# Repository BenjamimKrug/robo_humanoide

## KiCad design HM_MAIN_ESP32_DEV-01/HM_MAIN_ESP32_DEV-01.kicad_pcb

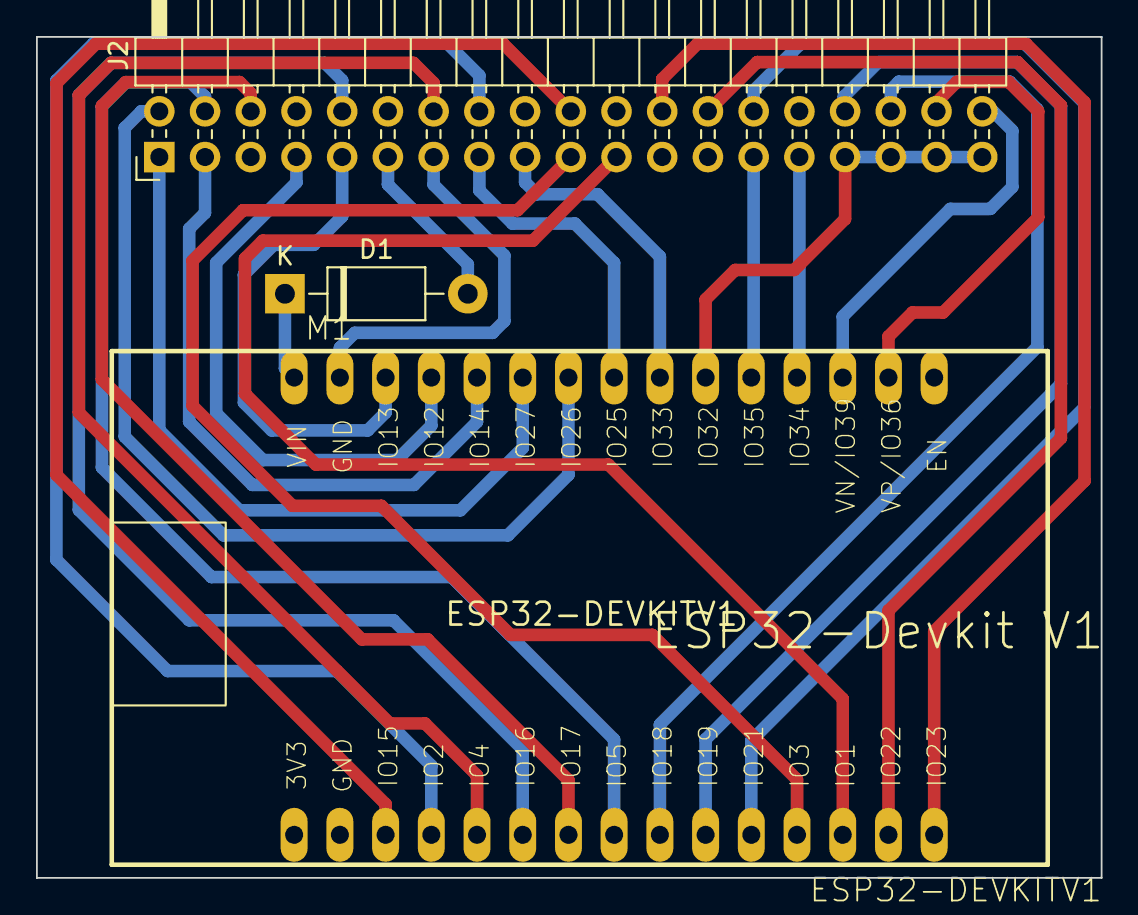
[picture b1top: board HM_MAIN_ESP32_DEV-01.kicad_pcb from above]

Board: 2 copper layers, 59.1 x 46.7 mm, 3 parts (0 on the bottom side), 28 nets.

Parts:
D1: 1N4007; D_DO-41_SOD81_P10.16mm_Horizontal
J2: Conn_02x19_Odd_Even; PinHeader_2x19_P2.54mm_Horizontal
M1: ESP32-DEVKITV1

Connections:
GND: J2.13, M1.GND@1 (GND)
I_SENS: J2.27, M1.D35 (IO35)
L_ANK_PWM: J2.1, M1.D27 (IO27)
L_ELB_PWM: J2.10, M1.D16 (IO16)
L_FT_ANGLE: J2.38, M1.D39 (VN-IO39)
L_FT_PWM: J2.2, M1.D26 (IO26)
L_HP_PWM: J2.9, M1.D13 (IO13)
L_KN_PWM: J2.3, M1.D14 (IO14)
L_SH_PWM: J2.6, M1.D17 (IO17)
L_TG_PWM: J2.7, M1.D12 (IO12)
L_TX_PWM: J2.4, M1.D5 (IO5)
MAIN_RX: J2.19, M1.D3 (IO3)
MAIN_TX: J2.21, M1.D1 (IO1)
unnamed: D1.1 (K), M1.VIN
R_ANK_PWM: J2.26, M1.D22 (IO22)
R_ELB_PWM: J2.20, M1.D15 (IO15)
R_FT_ANGLE: J2.36, M1.D36 (VP-OI36)
R_FT_PWM: J2.24, M1.D23 (IO23)
R_HP_PWM: J2.34, M1.D18 (IO18)
R_KN_PWM: J2.28, M1.D21 (IO21)
R_SH_PWM: J2.16, M1.D2 (IO2)
R_TG_PWM: J2.32, M1.D19 (IO19)
R_TX_PWM: J2.14, M1.D4 (IO4)
SCL: J2.15, M1.D25 (IO25)
SDA: J2.17, M1.D33 (IO33)
SERVO_CONTROL: J2.31, J2.33, J2.35, J2.37, M1.D32 (IO32)
SERVO_VCC: D1.2 (A), J2.11
SHUTOFF: J2.29, M1.D34 (IO34)

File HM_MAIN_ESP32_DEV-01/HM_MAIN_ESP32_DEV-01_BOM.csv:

"Id";"Designador";"Footprint";"Quantidade";"Designação";"Fornecedor e referência";
1;"M1";"ESP32-DEVKITV1";1;"ESP32-DEVKITV1";;;
2;"D1";"D_DO-41_SOD81_P10.16mm_Horizontal";1;"1N4007";;;
3;"J2";"PinHeader_2x19_P2.54mm_Horizontal";1;"Conn_02x19_Odd_Even";;;

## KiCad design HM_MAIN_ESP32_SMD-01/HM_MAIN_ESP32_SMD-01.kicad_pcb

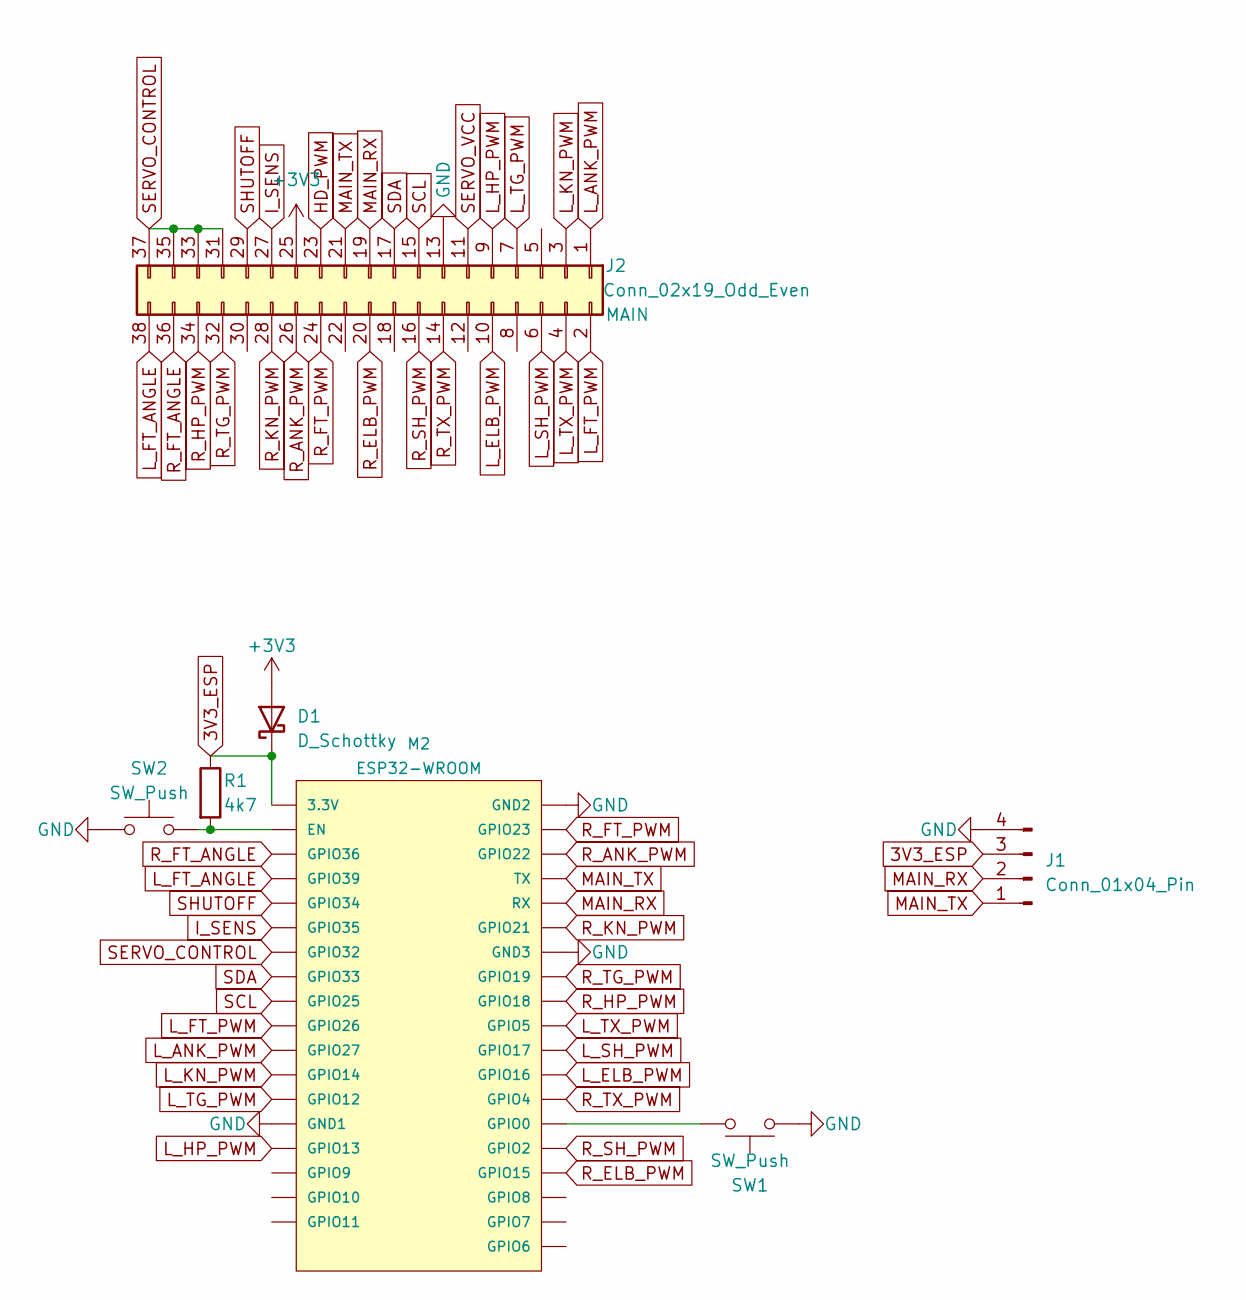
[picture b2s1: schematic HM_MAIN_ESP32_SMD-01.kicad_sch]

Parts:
D1: D_Schottky; D_A-405_P10.16mm_Horizontal
J1: Conn_01x04_Pin; PinHeader_1x04_P2.54mm_Horizontal
J2: Conn_02x19_Odd_Even; PinHeader_2x19_P2.54mm_Horizontal
M2: ESP32-WROOM
R1: 4k7; R_Axial_DIN0207_L6.3mm_D2.5mm_P7.62mm_Horizontal
SW1, SW2: SW_Push; SW_Tactile_SPST_Angled_PTS645Vx39-2LFS

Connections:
3V3_ESP: D1.1 (K), J1.3, M2.3V3 (3.3V), R1.1
+3V3: D1.2 (A), J2.25
GND: J1.4, J2.13, M2.GND1, M2.GND2, M2.GND3, SW1.1, SW2.1
HD_PWM: J2.23
I_SENS: J2.27, M2.IO35 (GPIO35)
L_ANK_PWM: J2.1, M2.IO27 (GPIO27)
L_ELB_PWM: J2.10, M2.IO16 (GPIO16)
L_FT_ANGLE: J2.38, M2.SENSOR_VN (GPIO39)
L_FT_PWM: J2.2, M2.IO26 (GPIO26)
L_HP_PWM: J2.9, M2.IO13 (GPIO13)
L_KN_PWM: J2.3, M2.IO14 (GPIO14)
L_SH_PWM: J2.6, M2.IO17 (GPIO17)
L_TG_PWM: J2.7, M2.IO12 (GPIO12)
L_TX_PWM: J2.4, M2.IO5 (GPIO5)
MAIN_RX: J1.2, J2.19, M2.RX
MAIN_TX: J1.1, J2.21, M2.TX
unnamed: M2.IO0 (GPIO0), SW1.2
unnamed: M2.EN, R1.2, SW2.2
R_ANK_PWM: J2.26, M2.IO22 (GPIO22)
R_ELB_PWM: J2.20, M2.IO15 (GPIO15)
R_FT_ANGLE: J2.36, M2.SENSOR_VP (GPIO36)
R_FT_PWM: J2.24, M2.IO23 (GPIO23)
R_HP_PWM: J2.34, M2.IO18 (GPIO18)
R_KN_PWM: J2.28, M2.IO21 (GPIO21)
R_SH_PWM: J2.16, M2.IO2 (GPIO2)
R_TG_PWM: J2.32, M2.IO19 (GPIO19)
R_TX_PWM: J2.14, M2.IO4 (GPIO4)
SCL: J2.15, M2.IO25 (GPIO25)
SDA: J2.17, M2.IO33 (GPIO33)
SERVO_CONTROL: J2.31, J2.33, J2.35, J2.37, M2.IO32 (GPIO32)
SERVO_VCC: J2.11
SHUTOFF: J2.29, M2.IO34 (GPIO34)

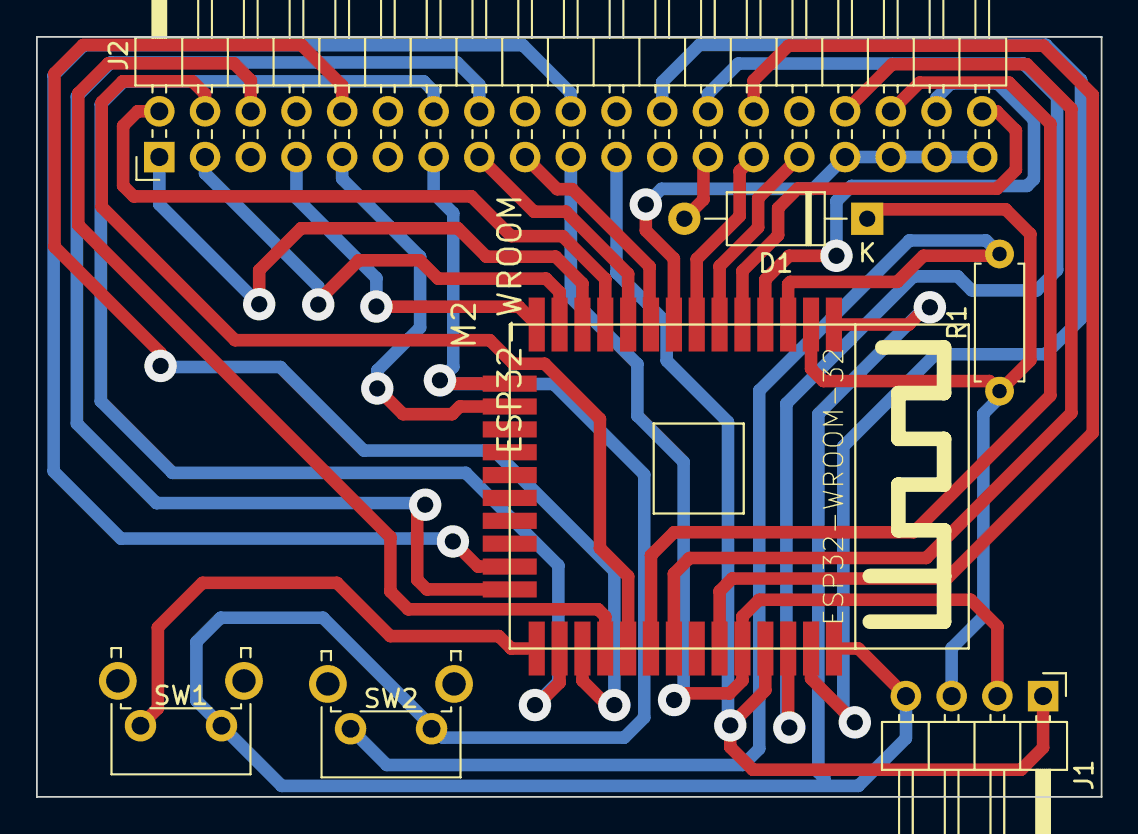
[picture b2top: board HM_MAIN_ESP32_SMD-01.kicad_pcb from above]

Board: 2 copper layers, 59.1 x 42.2 mm, 7 parts (0 on the bottom side), 30 nets.

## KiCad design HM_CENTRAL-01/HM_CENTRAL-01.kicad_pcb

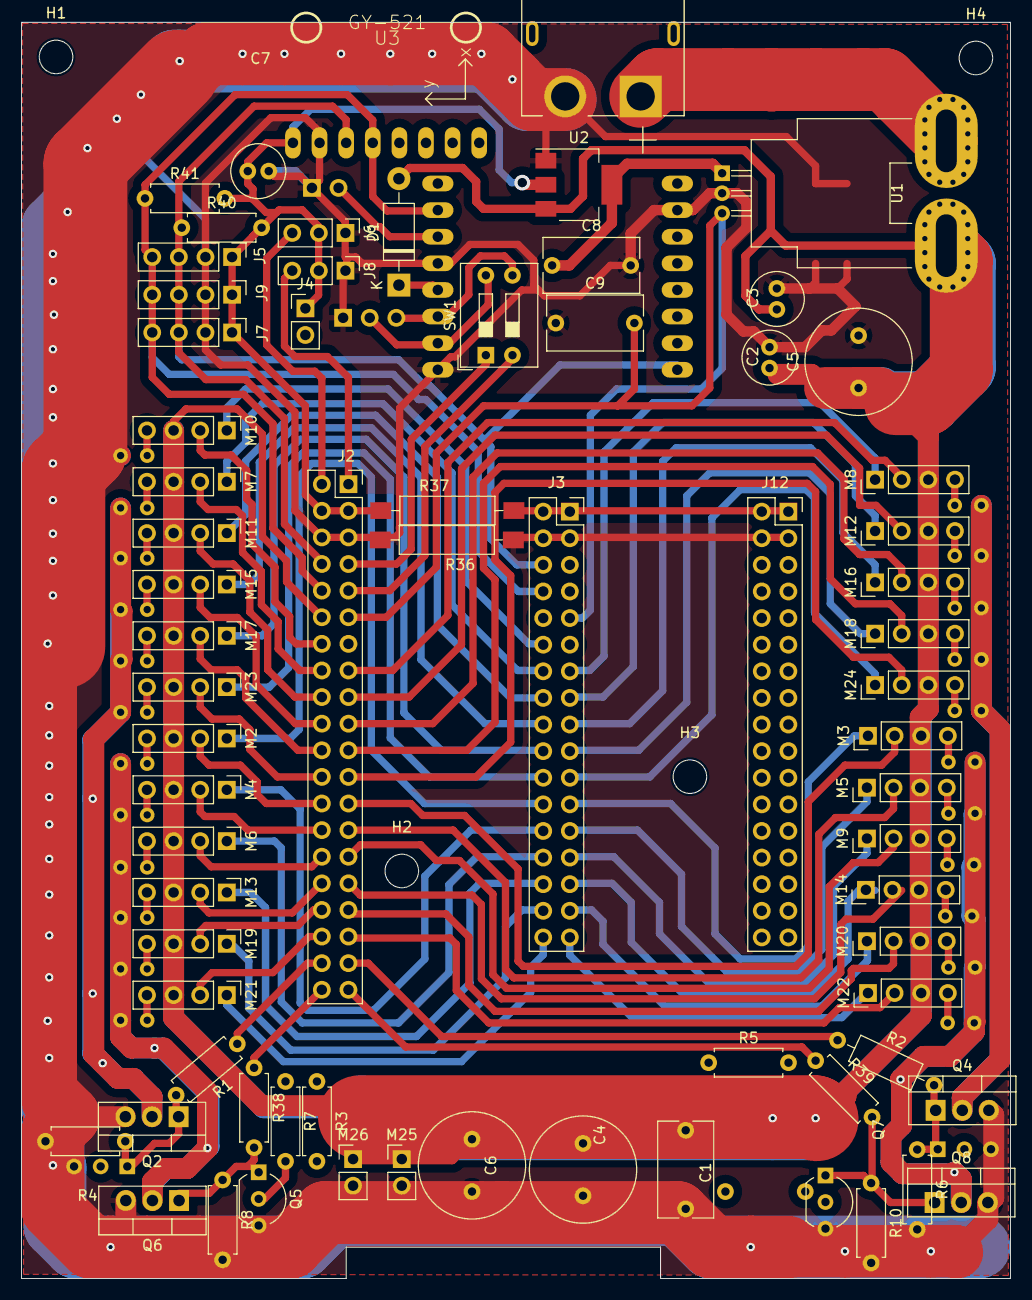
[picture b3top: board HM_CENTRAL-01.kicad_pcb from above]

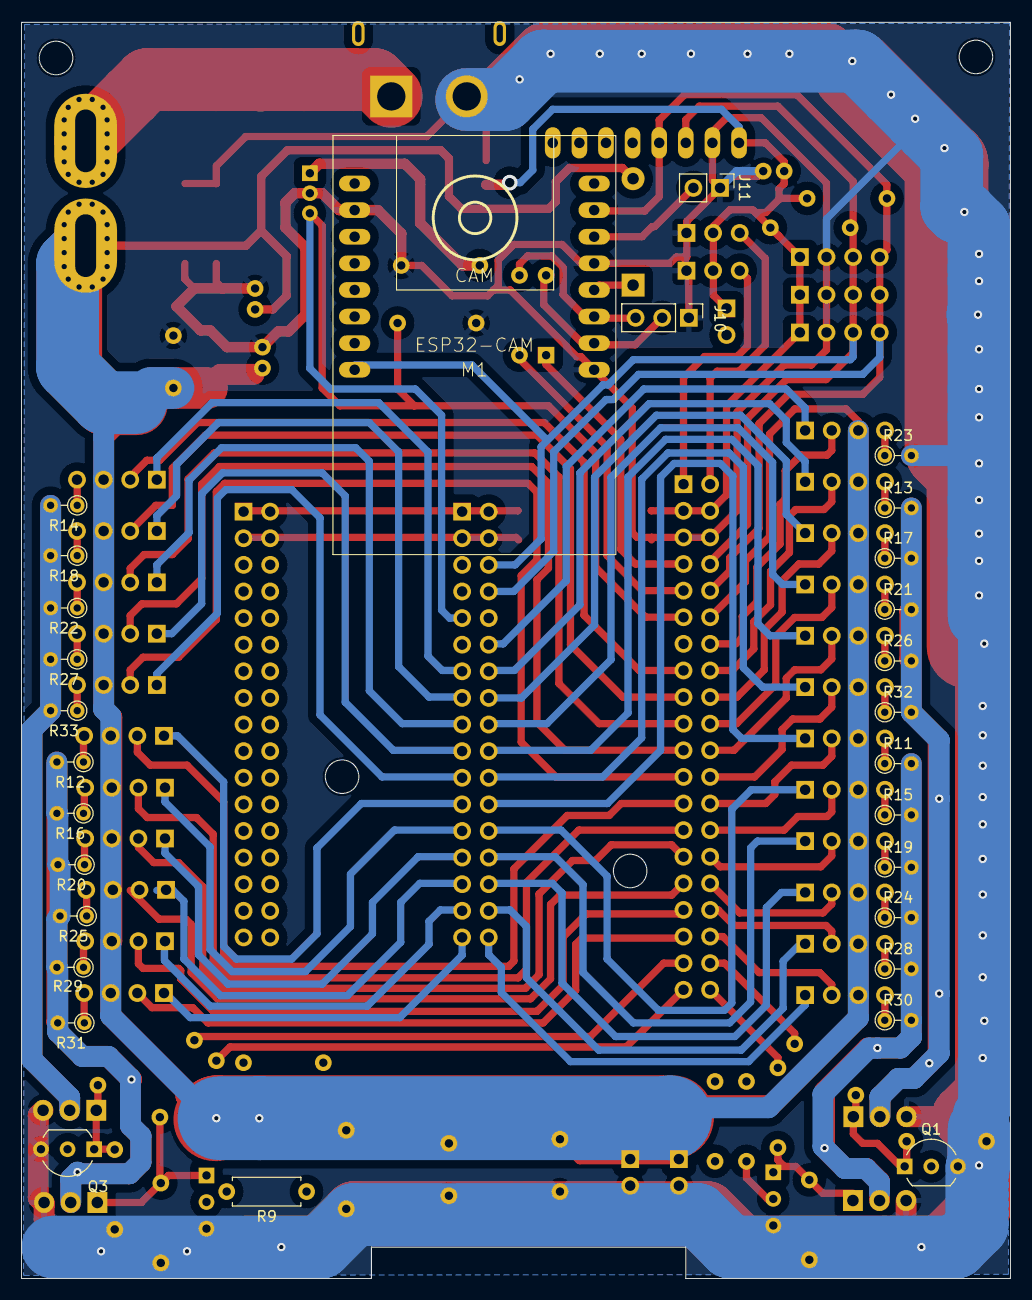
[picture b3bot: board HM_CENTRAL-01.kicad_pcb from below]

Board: 4 copper layers, 94.4 x 119.9 mm, 103 parts (29 on the bottom side), 101 nets.

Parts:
C1, C8, C9: 100nF; C_Rect_L9.0mm_W5.1mm_P7.50mm_MKT
C2: 10uF; C_Radial_D5.0mm_H11.0mm_P2.00mm
C3, C7: 100uF; C_Radial_D5.0mm_H11.0mm_P2.00mm
C4, C5: 1800uF; C_Radial_D10.0mm_H20.0mm_P5.00mm
C6: 2200uF; C_Radial_D10.0mm_H20.0mm_P5.00mm
D1: 1N4007; D_DO-41_SOD81_P10.16mm_Horizontal
H1, H2, H3, H4: MountingHole; MountingHole_3.2mm_M3
J1: XT60PW-M; AMASS_XT60PW-M
J2: Conn_02x20_Odd_Even; PinSocket_2x20_P2.54mm_Vertical
J3, J12: Conn_02x17_Odd_Even; PinSocket_2x17_P2.54mm_Vertical
J4, J11: Conn_01x02_Male; PinHeader_1x02_P2.54mm_Vertical
J5, J7, J9: Conn_01x04_Female; PinHeader_1x04_P2.54mm_Vertical
J6, J8, J10: Conn_01x03_Male; PinHeader_1x03_P2.54mm_Vertical
M1: ESP32-CAM
M2, M3, M4, M5, M6, M7, M8, M9, M10, M11, M12, M13, M14, M15, M16, M17, M18, M19, M20, M21, M22, M23, M24: Motor_Servo_with_Pot; PinHeader_1x04_P2.54mm_Vertical
M25, M26: Fan; PinHeader_1x02_P2.54mm_Vertical
Q1, Q3, Q5, Q7: BC337; TO-92_Inline_Wide
Q2, Q4, Q6, Q8: IRFZ44N; TO-220-3_Vertical
R1, R38, R39: 33K; R_Axial_DIN0207_L6.3mm_D2.5mm_P7.62mm_Horizontal
R2: 33K; R_Axial_DIN0207_L6.3mm_D2.5mm_P10.16mm_Horizontal
R3, R5, R7, R9: 1K; R_Axial_DIN0207_L6.3mm_D2.5mm_P7.62mm_Horizontal
R4, R6, R8, R10: 330K; R_Axial_DIN0207_L6.3mm_D2.5mm_P7.62mm_Horizontal
R11, R12, R13, R14, R15, R16, R17, R18, R19, R20, R21, R22, R23, R24, R25, R26, R27, R28, R29, R30, R31, R32, R33: Shunt_R; R_Axial_DIN0204_L3.6mm_D1.6mm_P2.54mm_Vertical
R36, R37: 0R; SMD_JUMPER
R40, R41: 4k7; R_Axial_DIN0207_L6.3mm_D2.5mm_P7.62mm_Horizontal
SW1: SW_DIP_x02; SW_DIP_SPSTx02_Slide_9.78x7.26mm_W7.62mm_P2.54mm
U1: ACS758xCB-050B-PFF; Allegro_CB_PFF
U2: AMS1117-3.3; SOT-223-3_TabPin2
U3: GY-521

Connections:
3V3: C7.1, C8.1, J2.3, J2.4, J3.1, J3.2, J4.1, J5.1, J6.2, J7.1, J8.2, J9.1, J12.1, J12.2, R37.1, R37.2, R40.2, R41.2, U1.1 (VCC), U2.2 (VO), U3.VCC
CAM_RX: J10.3, M1.14 (U0R), SW1.3
CAM_TX: J10.2, M1.15 (U0T), SW1.4
GND: C1.2, C2.2, C3.2, C4.2, C5.2, C6.2, C7.2, C8.2, C9.1, J1.2 (-), J2.5, J2.6, J3.3, J3.4, J5.2, J6.1, J7.2, J8.1, J9.2, J10.1, J11.1, J12.3, J12.4, M1.7 (GND_1), M1.12 (GND_2), M1.16 (GND_3), M25.2 (-), M26.2 (-), Q1.3 (E), Q2.3 (S), Q3.3 (E), Q4.3 (S), Q5.3 (E), Q6.3 (S), Q7.3 (E), Q8.3 (S), R4.2, R6.2, R8.2, R10.2, R23.2, R36.1, R36.2, U1.2 (GND), U2.1 (GND), U3.GND
HD_CURRENT: J12.12, M10.4 (-), R23.1
HD_POT: J3.12, M10.1 (POT)
HD_PWM: J2.14, M10.2 (PWM)
I_SENS: C9.2, J2.11, J3.9, J12.9, U1.3 (VIOUT)
L_ANK_CURRENT: J12.32, M19.4 (-), R28.1
L_ANK_POT: J3.32, M19.1 (POT)
L_ANK_PWM: J2.34, M19.2 (PWM)
L_ARM_CONTROL: J2.38, R1.1
L_ARM_GND: Q2.2 (D), R13.2, R17.2, R21.2, R26.2, R32.2
L_ELBR_CURRENT: J12.18, M15.4 (-), R21.1
L_ELBR_POT: J3.18, M15.1 (POT)
L_ELBR_PWM: J2.20, M15.2 (PWM)
L_ELB_CURRENT: J12.20, M17.4 (-), R26.1
L_ELB_POT: J3.20, M17.1 (POT)
L_ELB_PWM: J2.22, M17.2 (PWM)
L_FT_ANGLE: J2.2, J6.3
L_FT_CURRENT: J12.34, M21.4 (-), R30.1
L_FT_POT: J3.34, M21.1 (POT)
L_FT_PWM: J2.36, M21.2 (PWM)
L_HND_CURRENT: J12.22, M23.4 (-), R32.1
L_HND_POT: J3.22, M23.1 (POT)
L_HND_PWM: J2.24, M23.2 (PWM)
L_HP_CURRENT: J12.24, M2.4 (-), R11.1
L_HP_POT: J3.24, M2.1 (POT)
L_HP_PWM: J2.26, M2.2 (PWM)
L_KNR_CURRENT: J12.28, M6.4 (-), R19.1
L_KNR_POT: J3.28, M6.1 (POT)
L_KNR_PWM: J2.30, M6.2 (PWM)
L_KN_CURRENT: J12.30, M13.4 (-), R24.1
L_KN_POT: J3.30, M13.1 (POT)
L_KN_PWM: J2.32, M13.2 (PWM)
L_LEG_CONTROL: J2.40, R38.1
L_LEG_GND: Q6.2 (D), R11.2, R15.2, R19.2, R24.2, R28.2, R30.2
L_SH_CURRENT: J12.16, M11.4 (-), R17.1
L_SH_POT: J3.16, M11.1 (POT)
L_SH_PWM: J2.18, M11.2 (PWM)
L_TG_CURRENT: J12.26, M4.4 (-), R15.1
L_TG_POT: J3.26, M4.1 (POT)
L_TG_PWM: J2.28, M4.2 (PWM)
L_TX_CURRENT: J12.14, M7.4 (-), R13.1
L_TX_POT: J3.14, M7.1 (POT)
L_TX_PWM: J2.16, M7.2 (PWM)
MAIN_RX: J2.7, SW1.1
MAIN_TX: J2.9, SW1.2
unnamed: D1.1 (K), M1.13 (VCC)
unnamed: J1.1 (+), U1.5 (IP-)
unnamed: J11.2, M1.11 (IO0)
unnamed: Q1.2 (B), R3.2
unnamed: Q1.1 (C), Q2.1 (G), R1.2, R4.1
unnamed: Q3.2 (B), R5.2
unnamed: Q3.1 (C), Q4.1 (G), R2.2, R6.1
unnamed: Q5.2 (B), R7.2
unnamed: Q5.1 (C), Q6.1 (G), R8.1, R38.2
unnamed: Q7.2 (B), R9.2
unnamed: Q7.1 (C), Q8.1 (G), R10.1, R39.2
R_ANK_CURRENT: J12.31, M20.4 (-), R29.1
R_ANK_POT: J3.31, M20.1 (POT)
R_ANK_PWM: J2.33, M20.2 (PWM)
R_ARM_CONTROL: J2.37, R2.1
R_ARM_GND: Q4.2 (D), R14.2, R18.2, R22.2, R27.2, R33.2
R_ELBR_CURRENT: J12.17, M16.4 (-), R22.1
R_ELBR_POT: J3.17, M16.1 (POT)
R_ELBR_PWM: J2.19, M16.2 (PWM)
R_ELB_CURRENT: J12.19, M18.4 (-), R27.1
R_ELB_POT: J3.19, M18.1 (POT)
R_ELB_PWM: J2.21, M18.2 (PWM)
R_FT_ANGLE: J2.1, J8.3
R_FT_CURRENT: J12.33, M22.4 (-), R31.1
R_FT_POT: J3.33, M22.1 (POT)
R_FT_PWM: J2.35, M22.2 (PWM)
R_HND_CURRENT: J12.21, M24.4 (-), R33.1
R_HND_POT: J3.21, M24.1 (POT)
R_HND_PWM: J2.23, M24.2 (PWM)
R_HP_CURRENT: J12.23, M3.4 (-), R12.1
R_HP_POT: J3.23, M3.1 (POT)
R_HP_PWM: J2.25, M3.2 (PWM)
R_KNR_CURRENT: J12.27, M9.4 (-), R20.1
R_KNR_POT: J3.27, M9.1 (POT)
R_KNR_PWM: J2.29, M9.2 (PWM)
R_KN_CURRENT: J12.29, M14.4 (-), R25.1
R_KN_POT: J3.29, M14.1 (POT)
R_KN_PWM: J2.31, M14.2 (PWM)
R_LEG_CONTROL: J2.39, R39.1
R_LEG_GND: Q8.2 (D), R12.2, R16.2, R20.2, R25.2, R29.2, R31.2
R_SH_CURRENT: J12.15, M12.4 (-), R18.1
R_SH_POT: J3.15, M12.1 (POT)
R_SH_PWM: J2.17, M12.2 (PWM)
R_TG_CURRENT: J12.25, M5.4 (-), R16.1
R_TG_POT: J3.25, M5.1 (POT)
R_TG_PWM: J2.27, M5.2 (PWM)
R_TX_CURRENT: J12.13, M8.4 (-), R14.1
R_TX_POT: J3.13, M8.1 (POT)
R_TX_PWM: J2.15, M8.2 (PWM)
SCL: J2.8, J3.6, J5.3, J7.3, J9.3, J12.6, M1.1 (IO4), R40.1, U3.SCL
SDA: J2.10, J3.8, J5.4, J7.4, J9.4, J12.8, M1.10 (IO16), R41.1, U3.SDA
SERVO_VCC: C1.1, C2.1, C3.1, C4.1, C5.1, C6.1, D1.2 (A), J2.12, J3.10, J12.10, M2.3 (+), M3.3 (+), M4.3 (+), M5.3 (+), M6.3 (+), M7.3 (+), M8.3 (+), M9.3 (+), M10.3 (+), M11.3 (+), M12.3 (+), M13.3 (+), M14.3 (+), M15.3 (+), M16.3 (+), M17.3 (+), M18.3 (+), M19.3 (+), M20.3 (+), M21.3 (+), M22.3 (+), M23.3 (+), M24.3 (+), M25.1 (+), M26.1 (+), U1.4 (IP+), U2.3 (VI)
SHUTOFF: J2.13, J3.11, J4.2, J12.11, R3.1, R5.1, R7.1, R9.1

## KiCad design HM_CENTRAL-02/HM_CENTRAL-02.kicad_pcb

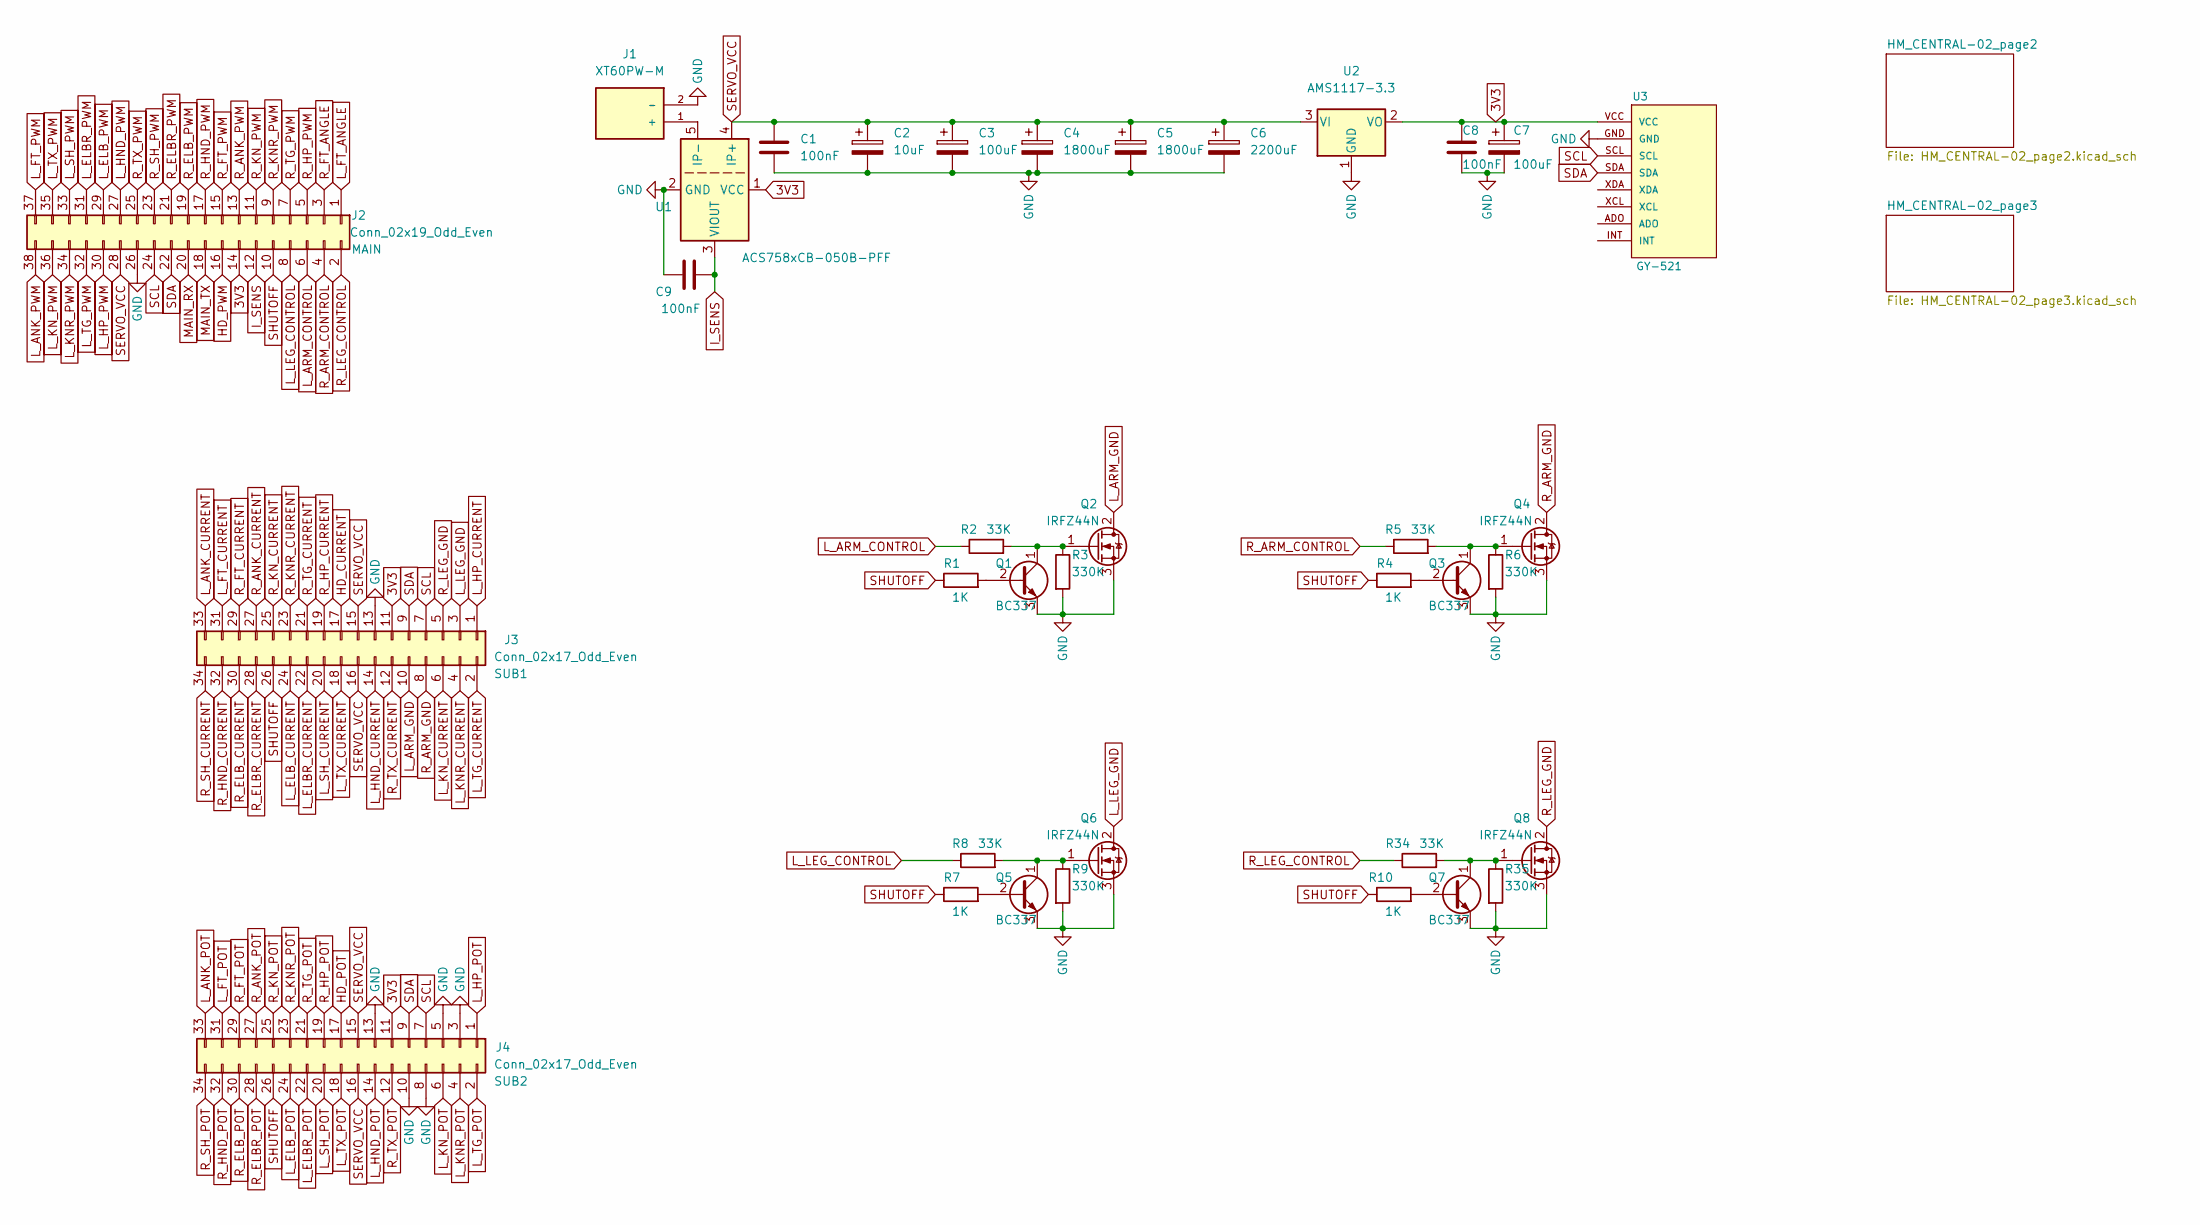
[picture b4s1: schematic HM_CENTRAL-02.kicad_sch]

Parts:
C1, C8, C9: 100nF; C_Rect_L9.0mm_W5.1mm_P7.50mm_MKT
C2: 10uF; C_Radial_D5.0mm_H11.0mm_P2.00mm
C3, C7: 100uF; C_Radial_D5.0mm_H11.0mm_P2.00mm
C4, C5: 1800uF; C_Radial_D10.0mm_H20.0mm_P5.00mm
C6: 2200uF; C_Radial_D10.0mm_H20.0mm_P5.00mm
J1: XT60PW-M; AMASS_XT60PW-M; PARTREV V1.2
J2: Conn_02x19_Odd_Even; PinSocket_2x19_P2.54mm_Vertical
J3, J4: Conn_02x17_Odd_Even; PinSocket_2x17_P2.54mm_Vertical
Q1, Q3, Q5, Q7: BC337; TO-92_Inline_Wide
Q2, Q4, Q6, Q8: IRFZ44N; TO-220-3_Vertical
R1, R4, R10: 1K; R_Axial_DIN0207_L6.3mm_D2.5mm_P7.62mm_Horizontal
R2, R34: 33K; R_Axial_DIN0207_L6.3mm_D2.5mm_P7.62mm_Horizontal
R3, R6, R9, R35: 330K; R_Axial_DIN0207_L6.3mm_D2.5mm_P7.62mm_Horizontal
R5, R8: 33K; R_Axial_DIN0207_L6.3mm_D2.5mm_P10.16mm_Horizontal
R7: 1K; R_Axial_DIN0207_L6.3mm_D2.5mm_P10.16mm_Horizontal
U1: ACS758xCB-050B-PFF; Allegro_CB_PFF
U2: AMS1117-3.3; SOT-223-3_TabPin2
U3: GY-521

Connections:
3V3: C7.1, C8.1, J2.14, J3.11, J4.11, U1.1 (VCC), U2.2 (VO), U3.VCC; also elsewhere on the board
GND: C1.2, C2.2, C3.2, C4.2, C5.2, C6.2, C7.2, C8.2, C9.1, J1.2 (-), J2.26, J3.13, J4.3, J4.5, J4.8, J4.10, J4.13, Q1.3 (E), Q2.3 (S), Q3.3 (E), Q4.3 (S), Q5.3 (E), Q6.3 (S), Q7.3 (E), Q8.3 (S), R3.2, R6.2, R9.2, R35.2, U1.2 (GND), U2.1 (GND), U3.GND; also elsewhere on the board
HD_CURRENT: J3.17; also elsewhere on the board
HD_POT: J4.17; also elsewhere on the board
HD_PWM: J2.16; also elsewhere on the board
I_SENS: C9.2, J2.12, U1.3 (VIOUT)
L_ANK_CURRENT: J3.33; also elsewhere on the board
L_ANK_POT: J4.33; also elsewhere on the board
L_ANK_PWM: J2.38; also elsewhere on the board
L_ARM_CONTROL: J2.6, R2.1
L_ARM_GND: J3.10, Q2.2 (D); also elsewhere on the board
L_ELBR_CURRENT: J3.22; also elsewhere on the board
L_ELBR_POT: J4.22; also elsewhere on the board
L_ELBR_PWM: J2.31; also elsewhere on the board
L_ELB_CURRENT: J3.24; also elsewhere on the board
L_ELB_POT: J4.24; also elsewhere on the board
L_ELB_PWM: J2.29; also elsewhere on the board
L_FT_ANGLE: J2.1; also elsewhere on the board
L_FT_CURRENT: J3.31; also elsewhere on the board
L_FT_POT: J4.31; also elsewhere on the board
L_FT_PWM: J2.37; also elsewhere on the board
L_HND_CURRENT: J3.14; also elsewhere on the board
L_HND_POT: J4.14; also elsewhere on the board
L_HND_PWM: J2.27; also elsewhere on the board
L_HP_CURRENT: J3.1; also elsewhere on the board
L_HP_POT: J4.1; also elsewhere on the board
L_HP_PWM: J2.30; also elsewhere on the board
L_KNR_CURRENT: J3.4; also elsewhere on the board
L_KNR_POT: J4.4; also elsewhere on the board
L_KNR_PWM: J2.34; also elsewhere on the board
L_KN_CURRENT: J3.6; also elsewhere on the board
L_KN_POT: J4.6; also elsewhere on the board
L_KN_PWM: J2.36; also elsewhere on the board
L_LEG_CONTROL: J2.8, R8.1
L_LEG_GND: J3.3, Q6.2 (D); also elsewhere on the board
L_SH_CURRENT: J3.20; also elsewhere on the board
L_SH_POT: J4.20; also elsewhere on the board
L_SH_PWM: J2.33; also elsewhere on the board
L_TG_CURRENT: J3.2; also elsewhere on the board
L_TG_POT: J4.2; also elsewhere on the board
L_TG_PWM: J2.32; also elsewhere on the board
L_TX_CURRENT: J3.18; also elsewhere on the board
L_TX_POT: J4.18; also elsewhere on the board
L_TX_PWM: J2.35; also elsewhere on the board
MAIN_RX: J2.20; also elsewhere on the board
MAIN_TX: J2.18; also elsewhere on the board
unnamed: J1.1 (+), U1.5 (IP-)
unnamed: Q1.2 (B), R1.2
unnamed: Q1.1 (C), Q2.1 (G), R2.2, R3.1
unnamed: Q3.2 (B), R4.2
unnamed: Q3.1 (C), Q4.1 (G), R5.2, R6.1
unnamed: Q5.2 (B), R7.2
unnamed: Q5.1 (C), Q6.1 (G), R8.2, R9.1
unnamed: Q7.2 (B), R10.2
unnamed: Q7.1 (C), Q8.1 (G), R34.2, R35.1
R_ANK_CURRENT: J3.27; also elsewhere on the board
R_ANK_POT: J4.27; also elsewhere on the board
R_ANK_PWM: J2.13; also elsewhere on the board
R_ARM_CONTROL: J2.4, R5.1
R_ARM_GND: J3.8, Q4.2 (D); also elsewhere on the board
R_ELBR_CURRENT: J3.28; also elsewhere on the board
R_ELBR_POT: J4.28; also elsewhere on the board
R_ELBR_PWM: J2.21; also elsewhere on the board
R_ELB_CURRENT: J3.30; also elsewhere on the board
R_ELB_POT: J4.30; also elsewhere on the board
R_ELB_PWM: J2.19; also elsewhere on the board
R_FT_ANGLE: J2.3; also elsewhere on the board
R_FT_CURRENT: J3.29; also elsewhere on the board
R_FT_POT: J4.29; also elsewhere on the board
R_FT_PWM: J2.15; also elsewhere on the board
R_HND_CURRENT: J3.32; also elsewhere on the board
R_HND_POT: J4.32; also elsewhere on the board
R_HND_PWM: J2.17; also elsewhere on the board
R_HP_CURRENT: J3.19; also elsewhere on the board
R_HP_POT: J4.19; also elsewhere on the board
R_HP_PWM: J2.5; also elsewhere on the board
R_KNR_CURRENT: J3.23; also elsewhere on the board
R_KNR_POT: J4.23; also elsewhere on the board
R_KNR_PWM: J2.9; also elsewhere on the board
R_KN_CURRENT: J3.25; also elsewhere on the board
R_KN_POT: J4.25; also elsewhere on the board
R_KN_PWM: J2.11; also elsewhere on the board
R_LEG_CONTROL: J2.2, R34.1
R_LEG_GND: J3.5, Q8.2 (D); also elsewhere on the board
R_SH_CURRENT: J3.34; also elsewhere on the board
R_SH_POT: J4.34; also elsewhere on the board
R_SH_PWM: J2.23; also elsewhere on the board
R_TG_CURRENT: J3.21; also elsewhere on the board
R_TG_POT: J4.21; also elsewhere on the board
R_TG_PWM: J2.7; also elsewhere on the board
R_TX_CURRENT: J3.12; also elsewhere on the board
R_TX_POT: J4.12; also elsewhere on the board
R_TX_PWM: J2.25; also elsewhere on the board
SCL: J2.24, J3.7, J4.7, U3.SCL; also elsewhere on the board
SDA: J2.22, J3.9, J4.9, U3.SDA; also elsewhere on the board
SERVO_VCC: C1.1, C2.1, C3.1, C4.1, C5.1, C6.1, J2.28, J3.15, J3.16, J4.15, J4.16, U1.4 (IP+), U2.3 (VI); also elsewhere on the board
SHUTOFF: J2.10, J3.26, J4.26, R1.1, R4.1, R7.1, R10.1; also elsewhere on the board
